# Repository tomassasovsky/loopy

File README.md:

# Segno

![coverage][coverage_badge]
[![style: very good analysis][very_good_analysis_badge]][very_good_analysis_link]
[![License: GPL v3][license_badge]][license_link]

Generated by the [Very Good CLI][very_good_cli_link] 🤖

Segno — a cross-platform desktop loopstation with a native low-latency audio engine

It can be driven hands-free from a USB MIDI foot controller — see
[docs/MIDI_FOOT_CONTROLLER.md](docs/MIDI_FOOT_CONTROLLER.md).

---

## Getting Started 🚀

This project contains 3 flavors:

- development
- staging
- production

To run the desired flavor either use the launch configuration in VSCode/Android Studio or use the following commands:

```sh
# Development
$ flutter run --flavor development --target lib/main_development.dart

# Staging
$ flutter run --flavor staging --target lib/main_staging.dart

# Production
$ flutter run --flavor production --target lib/main_production.dart
```

_\*Segno runs natively on macOS, Windows, and Linux._

> On desktop, flavors select the entrypoint via `--target`; `--flavor` only
> namespaces the build-output directory (there is no per-flavor app identity).
> Pass the matching `--target lib/main_<flavor>.dart` as shown above.
>
> Linux notes (PipeWire backend, Focusrite/`scarlett2` routing, renderer): see
> [docs/RUNNING_ON_LINUX.md](docs/RUNNING_ON_LINUX.md).

---

## Running Tests 🧪

To run all unit and widget tests use the following command:

```sh
$ very_good test --coverage --test-randomize-ordering-seed random
```

To view the generated coverage report you can use [lcov](https://github.com/linux-test-project/lcov).

```sh
# Generate Coverage Report
$ genhtml coverage/lcov.info -o coverage/

# Open Coverage Report
$ open coverage/index.html
```

---

## Bloc Lints 🔍

This project uses the [bloc_lint](https://pub.dev/packages/bloc_lint) package to enforce best practices using [bloc](https://pub.dev/packages/bloc).

To validate linter errors, run

```bash
dart run bloc_tools:bloc lint .
```

You can also validate with VSCode-based IDEs using the [official bloc extension](https://marketplace.visualstudio.com/items?itemName=FelixAngelov.bloc).

To learn more, visit https://bloclibrary.dev/lint/

---

## Working with Translations 🌐

This project follows the [official internationalization guide for Flutter][internationalization_link] using [ARB files][arb_documentation_link] for translations.

### Adding Strings

1. To add a new localizable string, open the `app_en.arb` file at `lib/l10n/arb/app_en.arb` and add a new key/value pair with the relevant description (optional):

```arb
{
    "@@locale": "en",
    "counterAppBarTitle": "Counter",
    "@counterAppBarTitle": {
        "description": "Text shown in the AppBar of the Counter Page"
    },
    "helloWorld": "Hello World",
    "@helloWorld": {
        "description": "Hello World greeting."
    }
}
```

1. Use the new string:

```dart
import 'package:segno/l10n/l10n.dart';

@override
Widget build(BuildContext context) {
  final l10n = context.l10n;
  return Text(l10n.helloWorld);
}
```

### Adding Supported Locales

Update the `CFBundleLocalizations` array in the `Info.plist` at `ios/Runner/Info.plist` to include the new locale.

```xml
    ...

    <key>CFBundleLocalizations</key>
	<array>
		<string>en</string>
		<string>es</string>
	</array>

    ...
```

### Adding Translations

1. For each supported locale, add a new ARB file in `lib/l10n/arb`:

```
├── l10n
│   ├── arb
│   │   ├── app_en.arb
│   │   └── app_es.arb
```

1. Add the translated strings to the new `.arb` file:

`app_es.arb`

```arb
{
    "@@locale": "es",
    "counterAppBarTitle": "Contador",
    "@counterAppBarTitle": {
        "description": "Texto mostrado en la AppBar de la página del contador"
    },
    "helloWorld": "Hola Mundo",
    "@helloWorld": {
        "description": "Saludo Hola Mundo."
    }    
}
```

### Generating Translations

To use the latest translations changes, you will need to generate them:

```sh
flutter gen-l10n --arb-dir="lib/l10n/arb"
```

Alternatively, run `flutter run` and code generation will take place automatically.

[coverage_badge]: coverage_badge.svg
[internationalization_link]: https://docs.flutter.dev/ui/internationalization
[arb_documentation_link]: https://github.com/google/app-resource-bundle
[license_badge]: https://img.shields.io/badge/license-GPLv3-blue.svg
[license_link]: https://www.gnu.org/licenses/gpl-3.0
[very_good_analysis_badge]: https://img.shields.io/badge/style-very_good_analysis-B22C89.svg
[very_good_analysis_link]: https://pub.dev/packages/very_good_analysis
[very_good_cli_link]: https://github.com/VeryGoodOpenSource/very_good_cli

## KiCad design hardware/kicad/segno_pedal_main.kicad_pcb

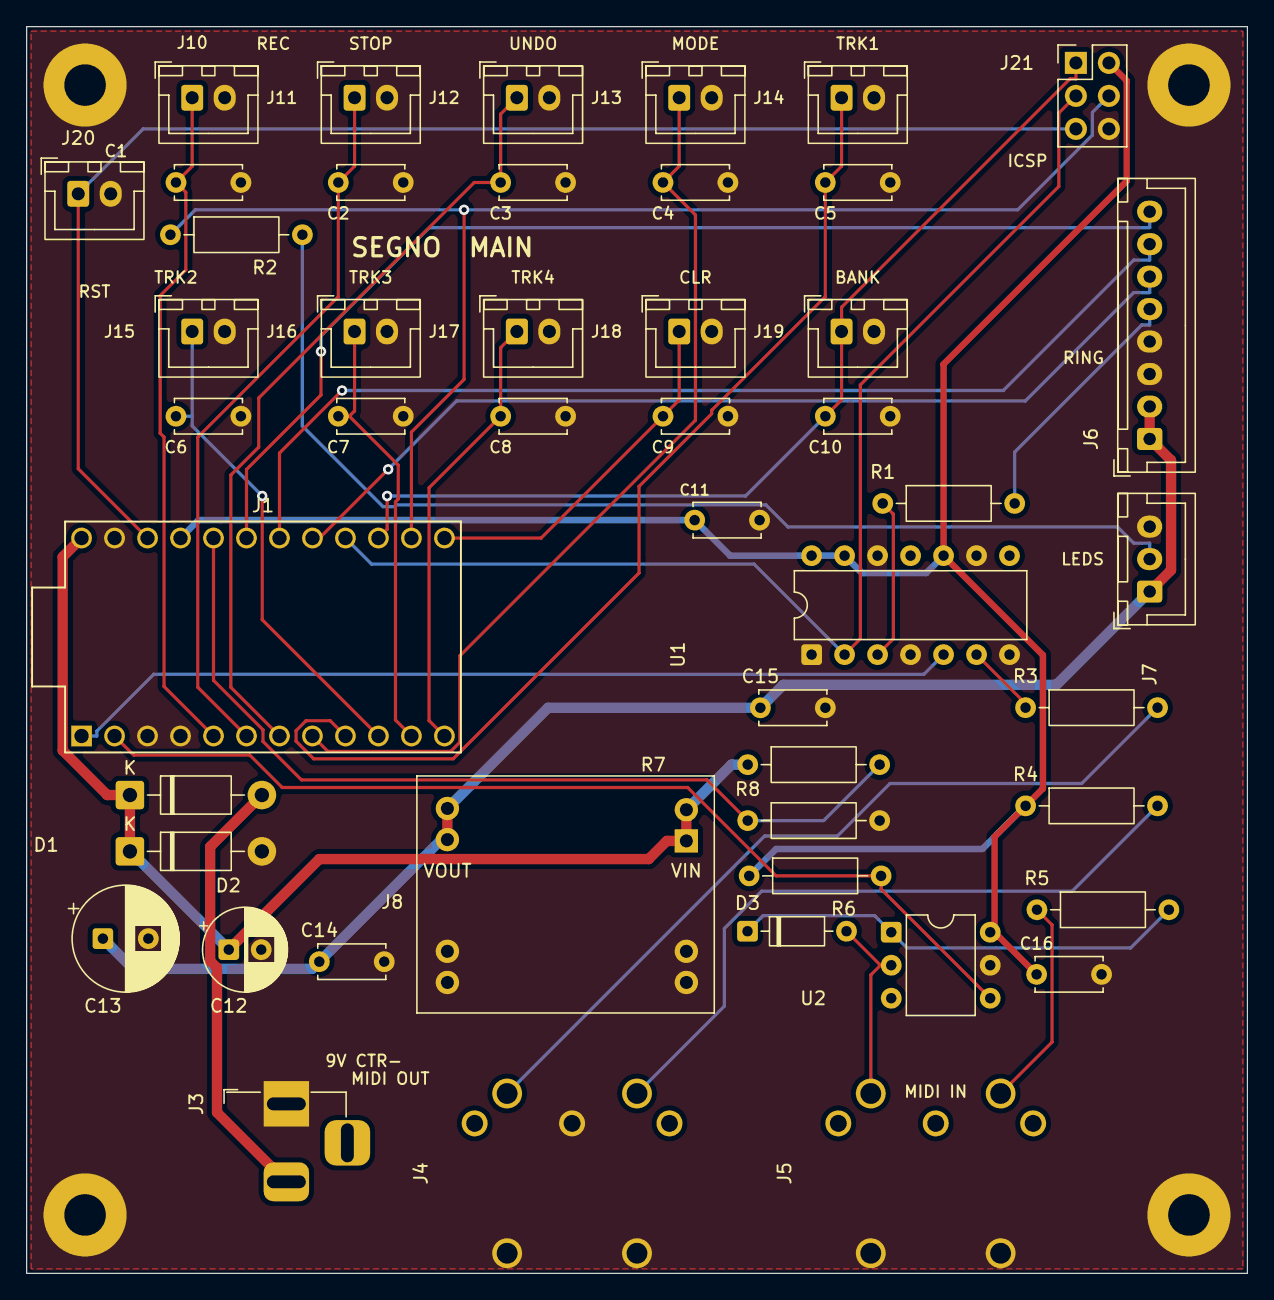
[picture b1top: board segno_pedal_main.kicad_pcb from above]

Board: 2 copper layers, 94.0 x 96.0 mm, 52 parts (0 on the bottom side), 33 nets.

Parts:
C1, C2, C3, C4, C5, C6, C7, C8, C9, C10, C11, C14, C15, C16: 100nF; C_Disc_D5.0mm_W2.5mm_P5.00mm
C12: 100uF; CP_Radial_D6.3mm_P2.50mm
C13: 470uF; CP_Radial_D8.0mm_P3.50mm
D1: 1N5817; D_DO-41_SOD81_P10.16mm_Horizontal
D2: P6KE13A; D_DO-41_SOD81_P10.16mm_Horizontal
D3: 1N4148; D_DO-35_SOD27_P7.62mm_Horizontal
H1, H2, H3, H4: MountingHole_3.2mm_M3_Pad
J1: ProMicro
J3: Barrel_Jack; BarrelJack_Horizontal
J4, J5: MIDI_DIN5_RA
J6: Conn_01x08; JST_XH_B8B-XH-A_1x08_P2.50mm_Vertical
J7: Conn_01x03; JST_XH_B3B-XH-A_1x03_P2.50mm_Vertical
J8: MP1584; BuckModule_MP1584
J10: FSW_RECPLAY; JST_XH_B2B-XH-A_1x02_P2.50mm_Vertical
J11: FSW_STOP; JST_XH_B2B-XH-A_1x02_P2.50mm_Vertical
J12: FSW_UNDO; JST_XH_B2B-XH-A_1x02_P2.50mm_Vertical
J13: FSW_MODE; JST_XH_B2B-XH-A_1x02_P2.50mm_Vertical
J14: FSW_TRACK1; JST_XH_B2B-XH-A_1x02_P2.50mm_Vertical
J15: FSW_TRACK2; JST_XH_B2B-XH-A_1x02_P2.50mm_Vertical
J16: FSW_TRACK3; JST_XH_B2B-XH-A_1x02_P2.50mm_Vertical
J17: FSW_TRACK4; JST_XH_B2B-XH-A_1x02_P2.50mm_Vertical
J18: FSW_CLEAR; JST_XH_B2B-XH-A_1x02_P2.50mm_Vertical
J19: FSW_BANK; JST_XH_B2B-XH-A_1x02_P2.50mm_Vertical
J20: RESET; JST_XH_B2B-XH-A_1x02_P2.50mm_Vertical
J21: ICSP; PinHeader_2x03_P2.54mm_Vertical
R1, R2: 330; R_Axial_DIN0207_L6.3mm_D2.5mm_P10.16mm_Horizontal
R3, R4, R5: 220; R_Axial_DIN0207_L6.3mm_D2.5mm_P10.16mm_Horizontal
R6: 10k; R_Axial_DIN0207_L6.3mm_D2.5mm_P10.16mm_Horizontal
R7: 100k; R_Axial_DIN0207_L6.3mm_D2.5mm_P10.16mm_Horizontal
R8: 47k; R_Axial_DIN0207_L6.3mm_D2.5mm_P10.16mm_Horizontal
U1: 74AHCT125N; DIP-14_W7.62mm
U2: H11L1; DIP-6_W7.62mm

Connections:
+5V: C11.1, C16.1, J1.21, J21.2, R4.1, R6.1, U1.10, U1.13, U1.14, U2.6
+5V_LED: C13.1, C14.1, C15.1, J6.1, J6.2, J7.1, J8.3
+9V: C12.1, D1.1, D2.1, J1.24, J8.1, R7.1
ENC_A: J1.17, J6.6
ENC_B: J1.18, J6.7
ENC_SW: J1.19, J6.8
GND: C1.2, C2.2, C3.2, C4.2, C5.2, C6.2, C7.2, C8.2, C9.2, C10.2, C11.2, C12.2, C13.2, C14.2, C15.2, C16.2, D2.2, H1.1, H2.1, H3.1, H4.1, J1.3, J1.4, J1.23, J3.1, J4.2, J4.6, J4.7, J5.6, J5.7, J6.3, J6.4, J7.3, J8.2, J8.4, J10.2, J11.2, J12.2, J13.2, J14.2, J15.2, J16.2, J17.2, J18.2, J19.2, J20.2, J21.6, R8.2, U1.1, U1.4, U1.7, U1.9, U1.12, U2.5
IND_DATA: J1.14, J21.4, R2.1
IND_DATA_OUT: J7.2, R2.2
LED_PWR_SENSE: J1.20, R7.2, R8.1
MIDI_OUT_BUF: R3.1, U1.6
unnamed: J4.5, R3.2
unnamed: J4.4, R4.2
unnamed: J5.4, R5.1
unnamed: D3.1, R5.2, U2.1
unnamed: D3.2, J5.5, U2.2
RING_DATA: J1.16, J21.3, U1.2
RING_DATA_BUF: R1.1, U1.3
RING_DATA_OUT: J6.5, R1.2
RST: J1.22, J20.1, J21.5
SW_BANK: C10.1, J1.15, J19.1, J21.1
SW_CLEAR: C9.1, J1.13, J18.1
SW_MODE: C4.1, J1.8, J13.1
SW_RECPLAY: C1.1, J1.5, J10.1
SW_STOP: C2.1, J1.6, J11.1
SW_TRACK1: C5.1, J1.9, J14.1
SW_TRACK2: C6.1, J1.10, J15.1
SW_TRACK3: C7.1, J1.11, J16.1
SW_TRACK4: C8.1, J1.12, J17.1
SW_UNDO: C3.1, J1.7, J12.1
UART_RX: J1.2, R6.2, U2.4
UART_TX: J1.1, U1.5
VIN_RAW: D1.2, J3.2

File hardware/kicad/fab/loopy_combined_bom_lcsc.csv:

LCSC,Comment,Value,Package,Qty,Designator,Notes
,Ceramic capacitor,100nF,C_Disc_D5.0mm_P5.00mm (THT),15,"MAIN:C1-C11,C14,C15 + RING:C2,C3",Any in-stock 100nF 50V THT disc or 5mm-pitch MLCC
C26761,Electrolytic,100uF,CP_Radial_D6.3mm_P2.50mm (>=16V),1,MAIN:C12,Chengx 100uF 25V leaded radial
C231191,Electrolytic,470uF,CP_Radial_D8.0mm_P3.50mm (>=16V),2,MAIN:C13 + RING:C1,Lelon 470uF 16V leaded radial
,Resistor,220R,Axial 1/4W DIN0207,3,MAIN:R3 R4 R5,Any in-stock 1/4W axial
,Resistor,330R,Axial 1/4W DIN0207,2,MAIN:R1 R2,Any in-stock 1/4W axial
,Resistor,10k,Axial 1/4W DIN0207,3,MAIN:R6 + RING:R1 R2,Any in-stock 1/4W axial
C354152,74AHCT125N,74AHCT125N,DIP-14,1,MAIN:U1,TI SN74AHCT125N quad buffer
C78588,H11L1,H11L1,DIP-6,1,MAIN:U2,Everlight Schmitt-output optocoupler (MIDI IN)
C163750,1N4148,1N4148,DO-35,1,MAIN:D3,Switching diode
C2935162,1N5817,1N5817,DO-41,1,MAIN:D1,Schottky 1A 20V reverse-prot (or C3062 MDD)
C294002,P6KE13A,P6KE13A,DO-41,1,MAIN:D2,TVS 13V 600W
C202365,Rotary encoder,EC11,EC11 vertical w/switch 20mm,1,RING:ENC1,ALPS EC11E type
C23689428,MIDI DIN-5,DIN-504 RA,MIDI_DIN5_RA,2,MAIN:J4 J5,Right-angle PCB DIN-5 jack
C319099,DC barrel jack,5.5/2.1 horizontal,BarrelJack_Horizontal,1,MAIN:J3,"DC-005 type - VERIFY pinout vs the KiCad BarrelJack_Horizontal footprint"
C158012,JST B2B-XH-A,2P 2.5mm,JST_XH vertical,11,MAIN:J10-J19 + J20,Board header (also buy XHP-2 housings + crimps for the wires)
C144394,JST B3B-XH-A,3P 2.5mm,JST_XH vertical,1,MAIN:J7,Indicator-strip header
C157972,JST B8B-XH-A,8P 2.5mm,JST_XH vertical,2,MAIN:J6 + RING:J1,Board-to-board link (one cable between them)
,Pin header,1x4 2.54mm,PinHeader_1x04,1,MAIN:J8,5V buck-module interface (snap from a 1x40 strip)
C5116479,Pin header,2x3 2.54mm,PinHeader_2x03,1,MAIN:J21,ICSP recovery header

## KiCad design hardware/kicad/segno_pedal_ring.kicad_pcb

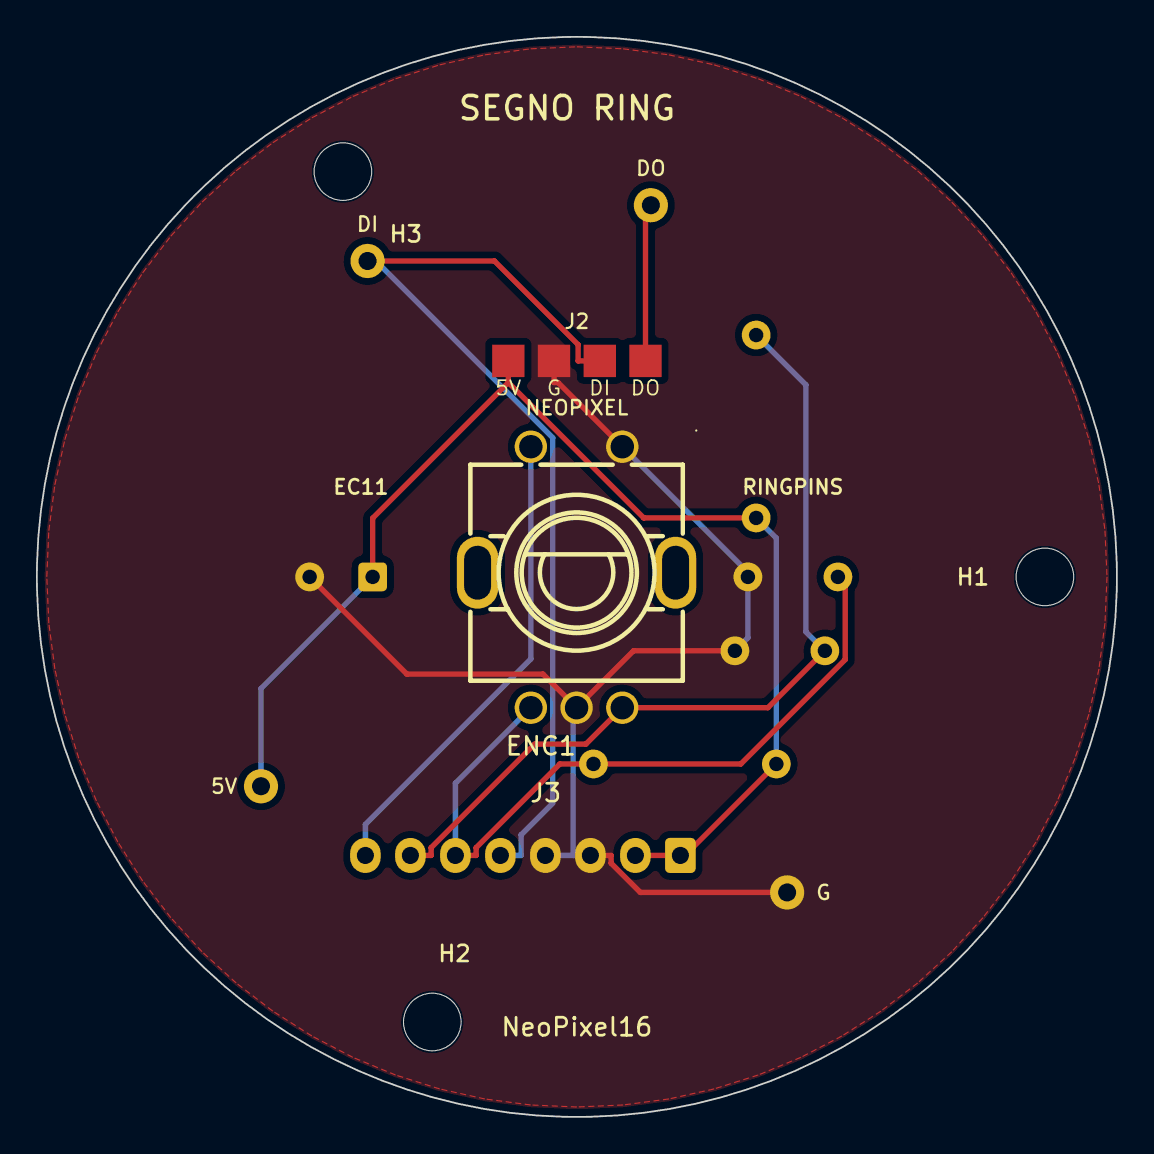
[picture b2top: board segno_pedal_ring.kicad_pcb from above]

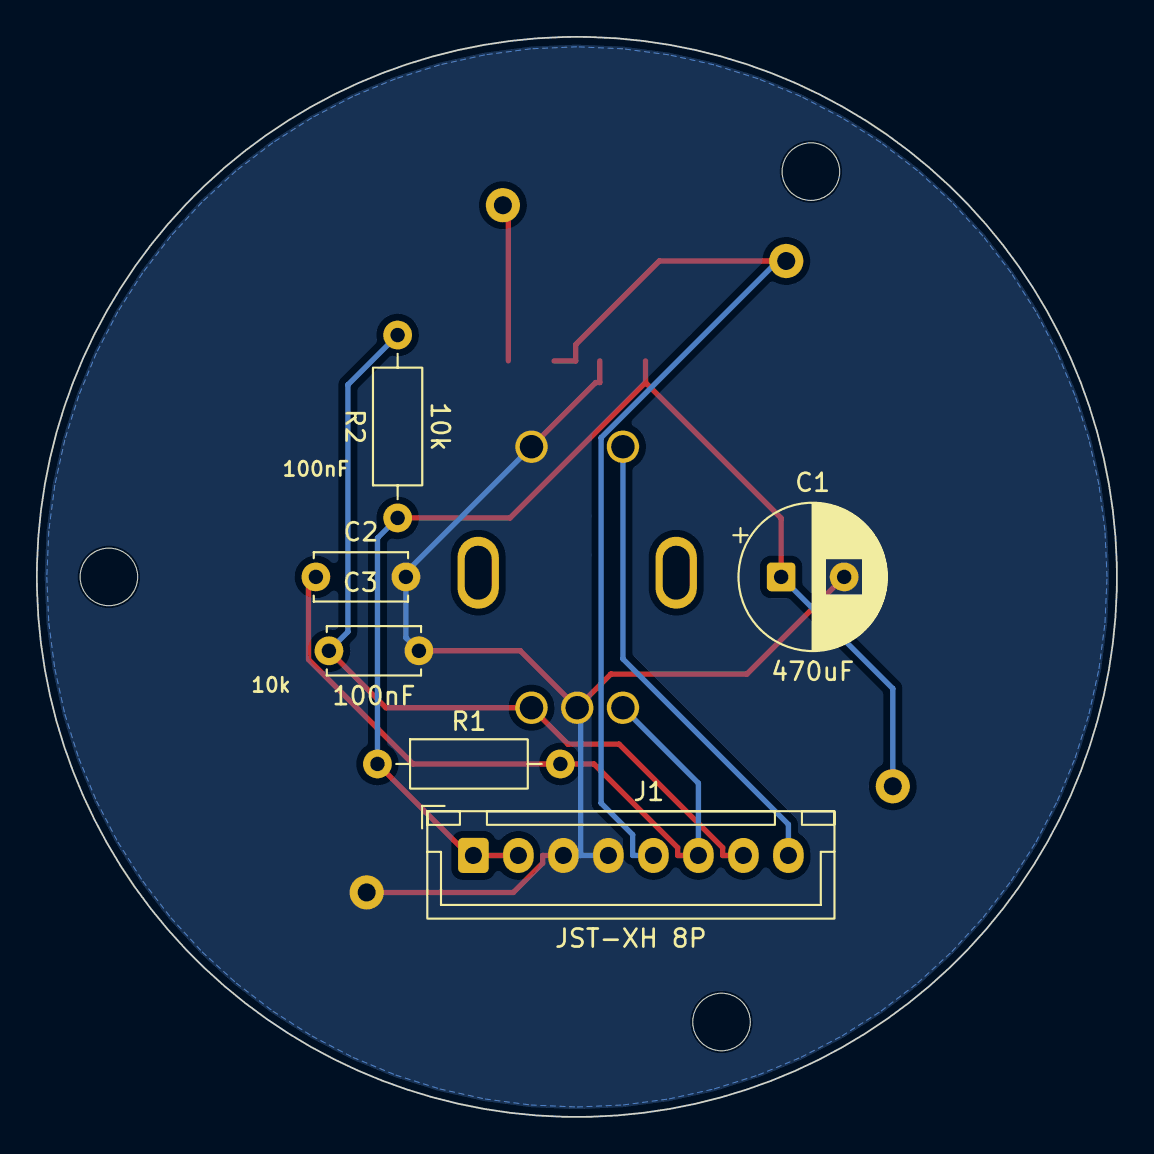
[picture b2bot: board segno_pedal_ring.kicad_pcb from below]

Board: 2 copper layers, 60.0 x 60.0 mm, 13 parts (6 on the bottom side), 7 nets.

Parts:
C1: 470uF; CP_Radial_D8.0mm_P3.50mm
C2, C3: 100nF; C_Disc_D5.0mm_W2.5mm_P5.00mm
ENC1: EC11; RotaryEncoder_EC11
H1, H2, H3: MountingHole_3.2mm_M3
J1: JST-XH 8P; JST_XH_B8B-XH-A_1x08_P2.50mm_Vertical
J2: NEOPIXEL; WirePads_1x04
J3: RINGPINS; ModuleMountPads_4
R1, R2: 10k; R_Axial_DIN0207_L6.3mm_D2.5mm_P10.16mm_Horizontal
RING1: NeoPixel16; NeoPixel_Ring16

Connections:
+5V_LED: C1.1, J1.1, J1.2, J2.1, J3.2, R1.1, R2.1
ENC_A: C2.1, ENC1.A, J1.6, R1.2
ENC_B: C3.1, ENC1.B, J1.7, R2.2
ENC_SW: ENC1.S1, J1.8
GND: C1.2, C2.2, C3.2, ENC1.C, ENC1.S2, J1.3, J1.4, J2.2, J3.3
RING_DATA: J1.5, J2.3, J3.1
RING_DOUT: J2.4, J3.4

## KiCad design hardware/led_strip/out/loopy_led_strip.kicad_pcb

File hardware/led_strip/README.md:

# segno LED strip

Single-LED WS2812B indicator puck for the Segno console: **one board per
indicator pedal**, sitting under that pedal's small pill diffuser slot in the
faceplate. One board is 16 x 8 mm, 2-layer, 1.6 mm, carrying **1x WS2812B
5050 addressable LED** (with its 100nF 0603 decoupling cap) and **castellated
half-hole pads on both 8 mm ends**.

```
 left edge                                right edge
 [5V ]──── +5V rail (top edge) ──────────────[5V ]
 [DI ]───────────D1──────────────────────────[DO ]
 [GND]──── GND rail (bottom edge) ───────────[GND]
           + full GND pour on the bottom copper
```

## How boards chain

Boards daisy-chain **pedal to pedal with three short wires** (5V / DATA /
GND, same pad order top-to-bottom on both ends — left-end DATA is DIN,
right-end DATA is DOUT) soldered to the castellated end pads. The
castellations also allow butting boards edge-to-edge (the LED sits 8 mm from
each end, so a butted pair keeps a 16 mm pitch) if a bar is ever wanted.

Console usage:

| row           | pedals with LEDs        | boards | LEDs |
| ------------- | ----------------------- | ------ | ---- |
| front row     | TRACK1..TRACK4          | 4      | 4    |
| mid row       | CLEAR, BANK             | 2      | 2    |
| per console   |                         | 6      | 6    |

Feed 5V/GND once (six indicator LEDs draw ~360 mA absolute worst case, far
less in practice). Data enters at DI on the first puck and daisy-chains
through every LED.

## Buy instead of build

Off-the-shelf single-WS2812B modules (round or square breakout pucks, sold in
tens for pocket change) are electrically identical — 5V/DIN/GND/DOUT, one
5050 — and drop into the same slots and wiring. This board exists for a
cleaner form factor and castellated wire pads; use whichever is at hand.

## Ordering (JLCPCB)

- 2-layer, 1.6 mm, any colour; the board is 16 x 8 mm — well under the
  100 x 100 mm cheap-tier limit.
- **Tick the "Castellated Holes" option.** The end pads are full plated 1.6 mm
  pads (0.8 mm drill) centred exactly on the board edge; the castellation
  process mills the edge through them leaving half-holes. Without the option
  the fab may flag the edge-breaking holes.
- Upload `out/segno_led_strip_gerbers.zip` (gerbers + Excellon drills).
- Parts if hand-placing: 4x WS2812B (5050 PLCC4), 4x 100nF 0603 per segment.

## Regenerating

The board is generated programmatically with KiCad 10's `pcbnew` module —
plain `python3` does **not** have it, use KiCad's bundled interpreter:

```sh
cd hardware/led_strip
/Applications/KiCad/KiCad.app/Contents/Frameworks/Python.framework/Versions/Current/bin/python3 ledstrip_pcb.py
```

This runs a geometry assertion suite, builds the board, fills the GND pour and
runs DRC via `kicad-cli` (the run fails loudly if DRC does), and writes to
`out/`:

- `segno_led_strip.kicad_pcb` — openable in KiCad
- `gerbers/` + `segno_led_strip_gerbers.zip` — fab package
- `drc.json` — full DRC report (expected: 0 violations, 0 unconnected)

All dimensions (LED count, pitch, rail widths, via rows…) are parameters at
the top of `ledstrip_pcb.py`; the netlist, routing and silkscreen are derived.

Design notes live as comments in the generator — in particular why the +5V
rail runs on the top edge and GND on the bottom (the WS2812B PLCC4 pinout
1=VDD 2=DOUT 3=GND 4=DIN puts VDD/GND on the package diagonal), and why the
data chain hops on the bottom copper (each LED's rail-to-rail decoupling cap
blocks the top-layer corridor).

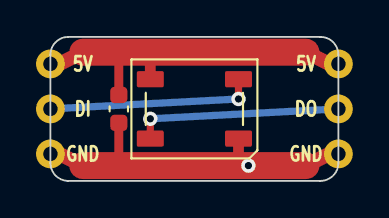
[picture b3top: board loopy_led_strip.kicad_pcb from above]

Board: 2 copper layers, 16.0 x 8.0 mm, 4 parts (0 on the bottom side), 4 nets.

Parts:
C1: C_0603_1608Metric
D1: LED_WS2812B_PLCC4_5.0x5.0mm_P3.2mm
J1, J2: castellated_edge

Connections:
+5V: C1.2, D1.1, J1.1, J2.1
DIN: D1.4, J1.2
DOUT: D1.2, J2.2
GND: C1.1, D1.3, J1.3, J2.3

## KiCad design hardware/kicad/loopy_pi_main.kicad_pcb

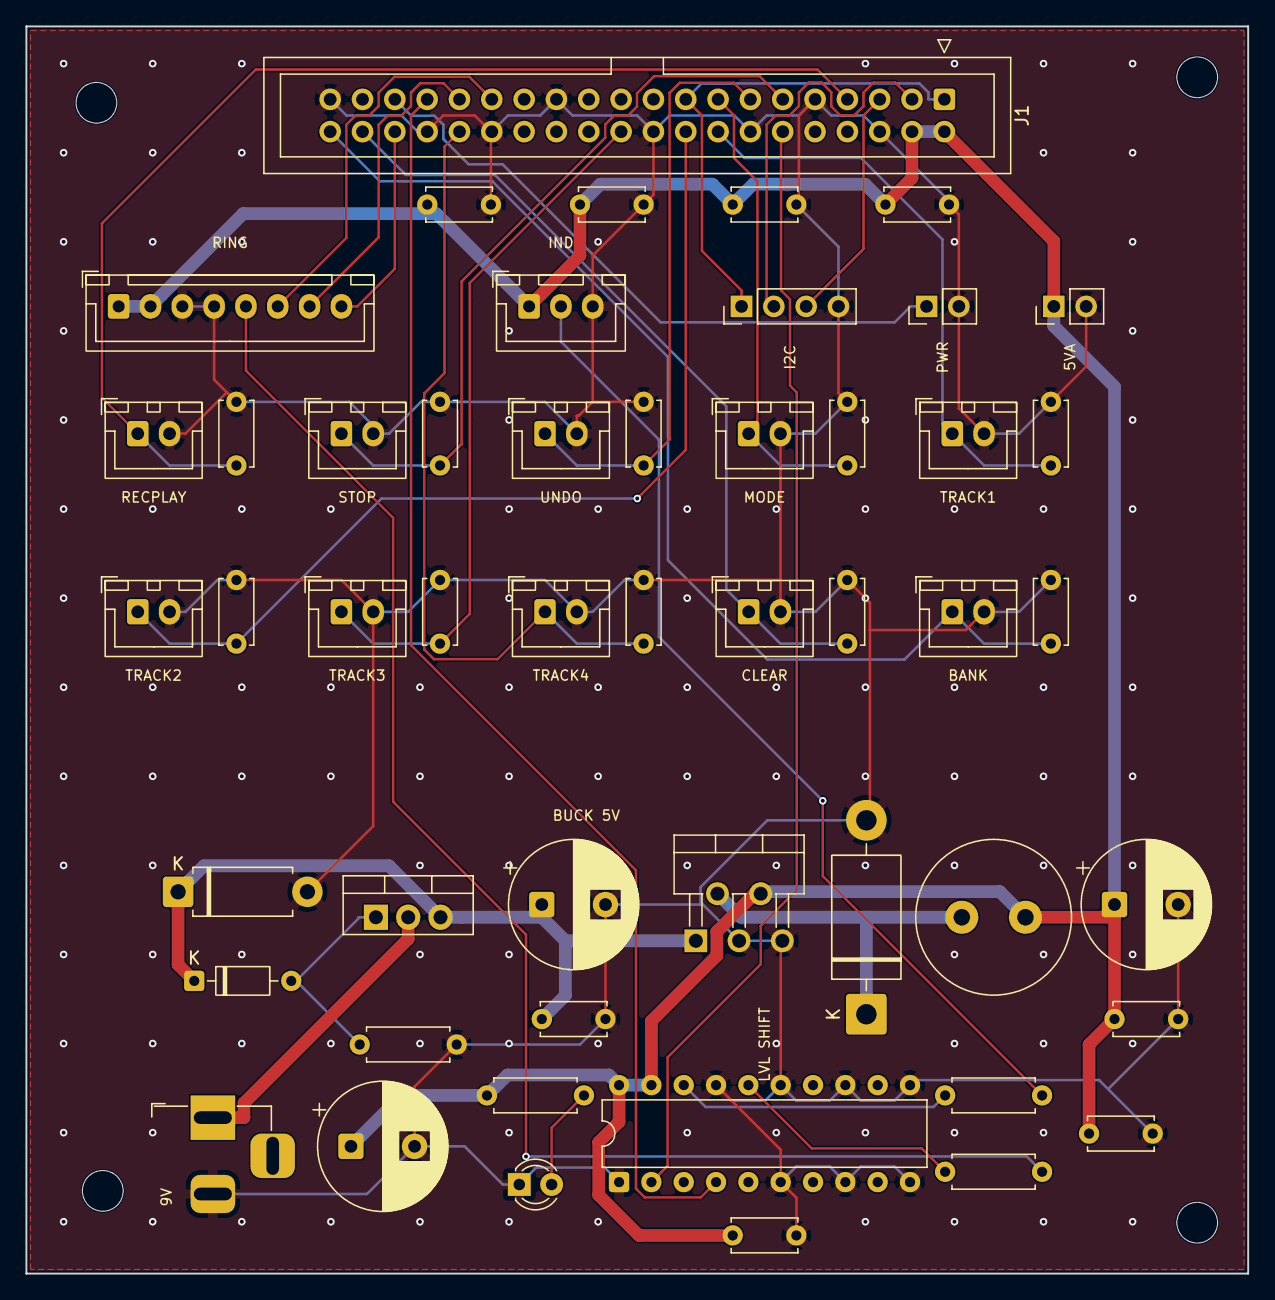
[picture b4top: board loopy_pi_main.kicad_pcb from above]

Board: 2 copper layers, 96.0 x 98.0 mm, 54 parts (0 on the bottom side), 30 nets.

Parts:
C1: 100uF; CP_Radial_D10.0mm_P5.00mm
C2, C4, C6, C7, C8, C9, C10, C11, C12, C13, C14, C15, C16, C17, C18, C19, C20, C21: 100nF; C_Disc_D5.0mm_W2.5mm_P5.00mm
C3: 680uF; CP_Radial_D10.0mm_P5.00mm
C5: 1000uF; CP_Radial_D10.0mm_P5.00mm
D1: P6KE15CA; D_DO-15_P10.16mm_Horizontal
D2: 12V; D_DO-35_SOD27_P7.62mm_Horizontal
D3: 1N5822; D_DO-201AD_P15.24mm_Horizontal
D4: PWR; LED_D3.0mm
H1, H2, H3, H4: MountingHole_3.2mm_M3
J1: RPi_GPIO_Ribbon; IDC-Header_2x20_P2.54mm_Vertical
J2: 9V; BarrelJack_Horizontal
J3: RECPLAY; JST_XH_B2B-XH-A_1x02_P2.50mm_Vertical
J4: STOP; JST_XH_B2B-XH-A_1x02_P2.50mm_Vertical
J5: UNDO; JST_XH_B2B-XH-A_1x02_P2.50mm_Vertical
J6: MODE; JST_XH_B2B-XH-A_1x02_P2.50mm_Vertical
J7: TRACK1; JST_XH_B2B-XH-A_1x02_P2.50mm_Vertical
J8: TRACK2; JST_XH_B2B-XH-A_1x02_P2.50mm_Vertical
J9: TRACK3; JST_XH_B2B-XH-A_1x02_P2.50mm_Vertical
J10: TRACK4; JST_XH_B2B-XH-A_1x02_P2.50mm_Vertical
J11: CLEAR; JST_XH_B2B-XH-A_1x02_P2.50mm_Vertical
J12: BANK; JST_XH_B2B-XH-A_1x02_P2.50mm_Vertical
J13: RING; JST_XH_B8B-XH-A_1x08_P2.50mm_Vertical
J14: IND; JST_XH_B3B-XH-A_1x03_P2.50mm_Vertical
J17: I2C; PinHeader_1x04_P2.54mm_Vertical
J18: PWR; PinHeader_1x02_P2.54mm_Vertical
J19: 5VA; PinHeader_1x02_P2.54mm_Vertical
L1: 33uH; L_Radial_D12.0mm_P5.00mm_Fastron_11P
Q1: IRF9540N; TO-220-3_Vertical
R1: 100k; R_Axial_DIN0207_L6.3mm_D2.5mm_P7.62mm_Horizontal
R2, R3: 330; R_Axial_DIN0207_L6.3mm_D2.5mm_P7.62mm_Horizontal
R4: 1k; R_Axial_DIN0207_L6.3mm_D2.5mm_P7.62mm_Horizontal
U1: BUCK 5V; TO-220-5_P3.4x3.7mm_StaggerOdd_Lead3.8mm_Vertical
U2: LVL SHIFT; DIP-20_W7.62mm

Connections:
+3V3: J1.1, J1.17, J17.1
+5V: C3.1, C4.1, C5.1, C6.1, C7.1, C8.1, C9.1, C10.1, C11.1, J1.2, J1.4, J13.1, J13.2, J14.1, J19.1, L1.2, R4.1, U1.4, U2.19, U2.20
+9V: C1.1, C2.1, D1.1, D2.1, Q1.3, U1.1
ENC_A: J1.29, J13.6
ENC_B: J1.31, J13.7
ENC_SW: J1.36, J13.8
GND: C1.2, C2.2, C3.2, C4.2, C5.2, C6.2, C7.2, C8.2, C9.2, C10.2, C11.2, C12.2, C13.2, C14.2, C15.2, C16.2, C17.2, C18.2, C19.2, C20.2, C21.2, D1.2, D3.2, D4.1, J1.6, J1.9, J1.14, J1.20, J1.25, J1.30, J1.34, J1.39, J2.2, J3.2, J4.2, J5.2, J6.2, J7.2, J8.2, J9.2, J10.2, J11.2, J12.2, J13.3, J13.4, J14.3, J17.4, J18.2, J19.2, R1.2, U1.3, U1.5, U2.1, U2.6, U2.8, U2.10, U2.11, U2.13, U2.15, U2.17
I2C_SCL: J1.5, J17.3
I2C_SDA: J1.3, J17.2
IND_BUF: R2.1, U2.18
IND_DATA: J1.12, U2.2
IND_DATA_OUT: J14.2, R2.2
PWR_BTN: J1.35, J18.1
PWR_GOOD: D4.2, R4.2
Q1_GATE: D2.2, Q1.1, R1.1
RING_BUF: R3.1, U2.16
RING_DATA: J1.33, U2.4
RING_DATA_OUT: J13.5, R3.2
SW_BANK: C21.1, J1.40, J12.1
SW_CLEAR: C20.1, J1.38, J11.1
SW_MODE: C15.1, J1.15, J6.1
SW_NODE: D3.1, L1.1, U1.2
SW_RECPLAY: C12.1, J1.7, J3.1
SW_STOP: C13.1, J1.11, J4.1
SW_TRACK1: C16.1, J1.16, J7.1
SW_TRACK2: C17.1, J1.18, J8.1
SW_TRACK3: C18.1, J1.22, J9.1
SW_TRACK4: C19.1, J1.32, J10.1
SW_UNDO: C14.1, J1.13, J5.1
VIN_RAW: J2.1, Q1.2

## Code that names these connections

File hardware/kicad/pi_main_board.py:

"""SKiDL generator for the Loopy **Pi main board** (standalone Raspberry Pi 4/5).

DIY / through-hole edition: every part is hand-solderable THT (TO-220 buck +
reverse-prot FET, DIP-20 buffer, axial resistors, disc/radial caps, leaded
diodes, 3mm LED).  The only SMD-ish parts are the connectors, which are all
through-hole anyway (GPIO socket, JST, barrel, pin headers).

The Raspberry Pi mounts via the 2x20 GPIO socket and runs the loopy audio engine
itself (audio I/O via a USB audio interface on the Pi).  This board carries
pedalboard power, the 10 footswitches, the EC11 encoder and the two WS2812
strips.  No MIDI / USB-device silicon -- the Pi reads the footswitches directly
over GPIO, and handles USB-MIDI controllers in software.

Reference designators are explicit so the layout script can cluster each part
functionally.  Symbol names/pins are for KiCad 10.

See ../loopy_pi_main_pcb_design.md.

Run (from hardware/kicad/):
    set KICAD8_SYMBOL_DIR=C:\\Program Files\\KiCad\\10.0\\share\\kicad\\symbols
    python pi_main_board.py
"""

from skidl import (
    Part, Net, generate_netlist, ERC, POWER,
    set_default_tool, KICAD8, lib_search_paths,
)

set_default_tool(KICAD8)
lib_search_paths[KICAD8].append(r"C:\Program Files\KiCad\10.0\share\kicad\symbols")

RES = "Resistor_THT:R_Axial_DIN0207_L6.3mm_D2.5mm_P7.62mm_Horizontal"
CER = "Capacitor_THT:C_Disc_D5.0mm_W2.5mm_P5.00mm"          # ceramic disc (100nF)
ELE = "Capacitor_THT:CP_Radial_D10.0mm_P5.00mm"            # radial electrolytic

def R(value, ref):
    return Part("Device", "R", value=value, ref=ref, footprint=RES)

def C(value, ref):
    return Part("Device", "C", value=value, ref=ref, footprint=CER)

def CP(value, ref):
    return Part("Device", "C_Polarized", value=value, ref=ref, footprint=ELE)

# ---- nets ------------------------------------------------------------------

gnd = Net("GND")
v5 = Net("+5V")          # single buck rail: powers the Pi AND the LED buffers
v3v3 = Net("+3V3")       # OUTPUT from the Pi (pins 1/17); used on the I2C header
v9 = Net("+9V")          # after reverse-polarity protection
vin_raw = Net("VIN_RAW")  # barrel center pin (before the P-FET)
q1g = Net("Q1_GATE")
pgood = Net("PWR_GOOD")
ind_data = Net("IND_DATA")          # GPIO18 / PWM0 -> buffer
ind_data_out = Net("IND_DATA_OUT")  # buffer + 330R -> off-board strip
ind_buf = Net("IND_BUF")
ring_data = Net("RING_DATA")        # GPIO13 / PWM1 -> buffer
ring_data_out = Net("RING_DATA_OUT")  # buffer + 330R -> cable
ring_buf = Net("RING_BUF")
sda = Net("I2C_SDA")
scl = Net("I2C_SCL")
pwrbtn = Net("PWR_BTN")
encA = Net("ENC_A")
encB = Net("ENC_B")
encSW = Net("ENC_SW")

# ---- J1: Raspberry Pi 4/5 40-pin GPIO header (ribbon-connected) -------------

# 2x20 male boxed IDC header on the TOP side. A 40-pin ribbon cable links it to
# the Pi's GPIO header, so this board sits separately instead of stacking on the
# Pi (avoids the Pi's tall USB/Ethernet jacks fouling the board). Pinout is 1:1
# with the Pi via a straight-through ribbon.
pi = Part("Connector", "Raspberry_Pi_4",
          footprint="Connector_IDC:IDC-Header_2x20_P2.54mm_Vertical",
          ref="J1", value="RPi_GPIO_Ribbon")
pi[2, 4] += v5
pi[1, 17] += v3v3
pi[6, 9, 14, 20, 25, 30, 34, 39] += gnd
pi[3] += sda
pi[5] += scl
pi[12] += ind_data       # GPIO18 PWM0
pi[33] += ring_data      # GPIO13 PWM1
pi[29] += encA           # GPIO5
pi[31] += encB           # GPIO6
pi[36] += encSW          # GPIO16
pi[35] += pwrbtn         # GPIO19
# GPIO14/15 (pins 8/10) and SPI0 (19/21/23/24/26) left free.

# footswitches -> Pi GPIO (active-low, internal pull-ups) + 100nF debounce each
fsw = [("RECPLAY", 7), ("STOP", 11), ("UNDO", 13), ("MODE", 15), ("TRACK1", 16),
       ("TRACK2", 18), ("TRACK3", 22), ("TRACK4", 32), ("CLEAR", 38), ("BANK", 40)]
for i, (name, pin) in enumerate(fsw):
    n = Net("SW_" + name)
    pi[pin] += n
    jp = Part("Connector_Generic", "Conn_01x02",
              footprint="Connector_JST:JST_XH_B2B-XH-A_1x02_P2.50mm_Vertical",
              ref="J%d" % (3 + i), value="FSW_" + name)
    jp[1] += n
    jp[2] += gnd
    C("100nF", "C%d" % (12 + i))[1, 2] += n, gnd   # debounce cap (C12..C21)

# ---- Power: 9V barrel -> reverse-prot P-FET -> 5V buck module -> +5V --------

j2 = Part("Connector", "Barrel_Jack",
          footprint="Connector_BarrelJack:BarrelJack_Horizontal", ref="J2")
j2[1] += vin_raw        # center (positive)
j2[2] += gnd            # sleeve
# High-side reverse-polarity P-FET: IRF9540N (TO-220, -100V/-23A, G=1,D=2,S=3).
# DRAIN=input, SOURCE=load(+9V), GATE=GND -> body diode conducts input->load,
# blocks on reverse polarity.  Lossless (vs a series Schottky) and DIY-friendly.
q1 = Part("Transistor_FET", "IRF9540N",
          footprint="Package_TO_SOT_THT:TO-220-3_Vertical", ref="Q1")
q1["S"] += v9
q1["G"] += q1g
q1["D"] += vin_raw
R("100k", "R1")[1, 2] += q1g, gnd
Part("Device", "D_Zener", value="12V",
     footprint="Diode_THT:D_DO-35_SOD27_P7.62mm_Horizontal", ref="D2")[1, 2] += v9, q1g
Part("Device", "D_TVS", value="P6KE15CA",
     footprint="Diode_THT:D_DO-15_P10.16mm_Horizontal", ref="D1")[1, 2] += v9, gnd
CP("100uF", "C1")[1, 2] += v9, gnd        # input bulk
C("100nF", "C2")[1, 2] += v9, gnd         # input HF bypass

# 5V buck MODULE (synchronous, >90% efficient -> runs cool, NO heatsink needed),
# replacing the LM2596 + its catch diode + inductor. 3-pin 7805-compatible
# pinout (1=VIN, 2=GND, 3=VOUT): a Recom R-78H5.0-2.0 (2A) drops straight in; for
# full Pi 3A headroom, wire a higher-current module (e.g. Pololu D36V28F5) to
# these three pads.
u1 = Part("Regulator_Linear", "L7805",
          footprint="Package_TO_SOT_THT:TO-220-3_Vertical",
          ref="U1", value="DCDC_5V_Buck")
u1[1] += v9            # VIN
u1[2] += gnd           # GND
u1[3] += v5            # VOUT (fixed 5V)
CP("680uF", "C3")[1, 2] += v5, gnd        # output bulk
C("100nF", "C4")[1, 2] += v5, gnd         # output HF bypass

# +5V bulk for Pi inrush + 4x 100nF spread along the GPIO power pins
CP("1000uF", "C5")[1, 2] += v5, gnd
for r in ("C6", "C7", "C8", "C9"):
    C("100nF", r)[1, 2] += v5, gnd

# power-good LED (Device:LED pin1=K, pin2=A)
R("1k", "R4")[1, 2] += v5, pgood
Part("Device", "LED", value="PWR",
     footprint="LED_THT:LED_D3.0mm", ref="D4")[2, 1] += pgood, gnd

# ---- WS2812 level shifters: one 74HCT244 DIP, two of its buffers -----------
# AHCT/HCT TTL inputs accept the Pi's 3.3V as a valid HIGH and output a clean
# 0-5V.  244 group-1: 1A0(2)->1Y0(18) indicator, 1A1(4)->1Y1(16) ring.
u2 = Part("74xx", "74HCT244", footprint="Package_DIP:DIP-20_W7.62mm", ref="U2")
u2[20] += v5            # VCC
u2[10] += gnd          # GND
u2[1] += gnd           # 1OE = enabled
u2[19] += v5           # 2OE = disabled (group 2 unused)
u2[2] += ind_data;  u2[18] += ind_buf
u2[4] += ring_data; u2[16] += ring_buf
u2[6, 8, 11, 13, 15, 17] += gnd   # tie unused inputs low
R("330", "R2")[1, 2] += ind_buf, ind_data_out
R("330", "R3")[1, 2] += ring_buf, ring_data_out
C("100nF", "C10")[1, 2] += v5, gnd

# ---- ring-board connector (8-pin, SAME pinout as the original ring board) ---

j13 = Part("Connector_Generic", "Conn_01x08",
           footprint="Connector_JST:JST_XH_B8B-XH-A_1x08_P2.50mm_Vertical", ref="J13")
j13[1, 2] += v5
j13[3, 4] += gnd
j13[5] += ring_data_out
j13[6] += encA
j13[7] += encB
j13[8] += encSW

# ---- indicator-LED breakout (3-pin) ----------------------------------------

j14 = Part("Connector_Generic", "Conn_01x03",
           footprint="Connector_JST:JST_XH_B3B-XH-A_1x03_P2.50mm_Vertical", ref="J14")
j14[1] += v5
j14[2] += ind_data_out
j14[3] += gnd
C("100nF", "C11")[1, 2] += v5, gnd

# ---- I2C / power-button / 5V-aux headers -----------------------------------

j17 = Part("Connector_Generic", "Conn_01x04",
           footprint="Connector_PinHeader_2.54mm:PinHeader_1x04_P2.54mm_Vertical", ref="J17")
j17[1] += v3v3; j17[2] += sda; j17[3] += scl; j17[4] += gnd

j18 = Part("Connector_Generic", "Conn_01x02",
           footprint="Connector_PinHeader_2.54mm:PinHeader_1x02_P2.54mm_Vertical", ref="J18")
j18[1] += pwrbtn; j18[2] += gnd

j19 = Part("Connector_Generic", "Conn_01x02",
           footprint="Connector_PinHeader_2.54mm:PinHeader_1x02_P2.54mm_Vertical", ref="J19")
j19[1] += v5; j19[2] += gnd        # external 5V bypass (only when U1 unpopulated)

# ---- ERC bookkeeping -------------------------------------------------------

for _n in (gnd, v5, v3v3, v9, vin_raw):
    _n.drive = POWER

ERC()
generate_netlist()
